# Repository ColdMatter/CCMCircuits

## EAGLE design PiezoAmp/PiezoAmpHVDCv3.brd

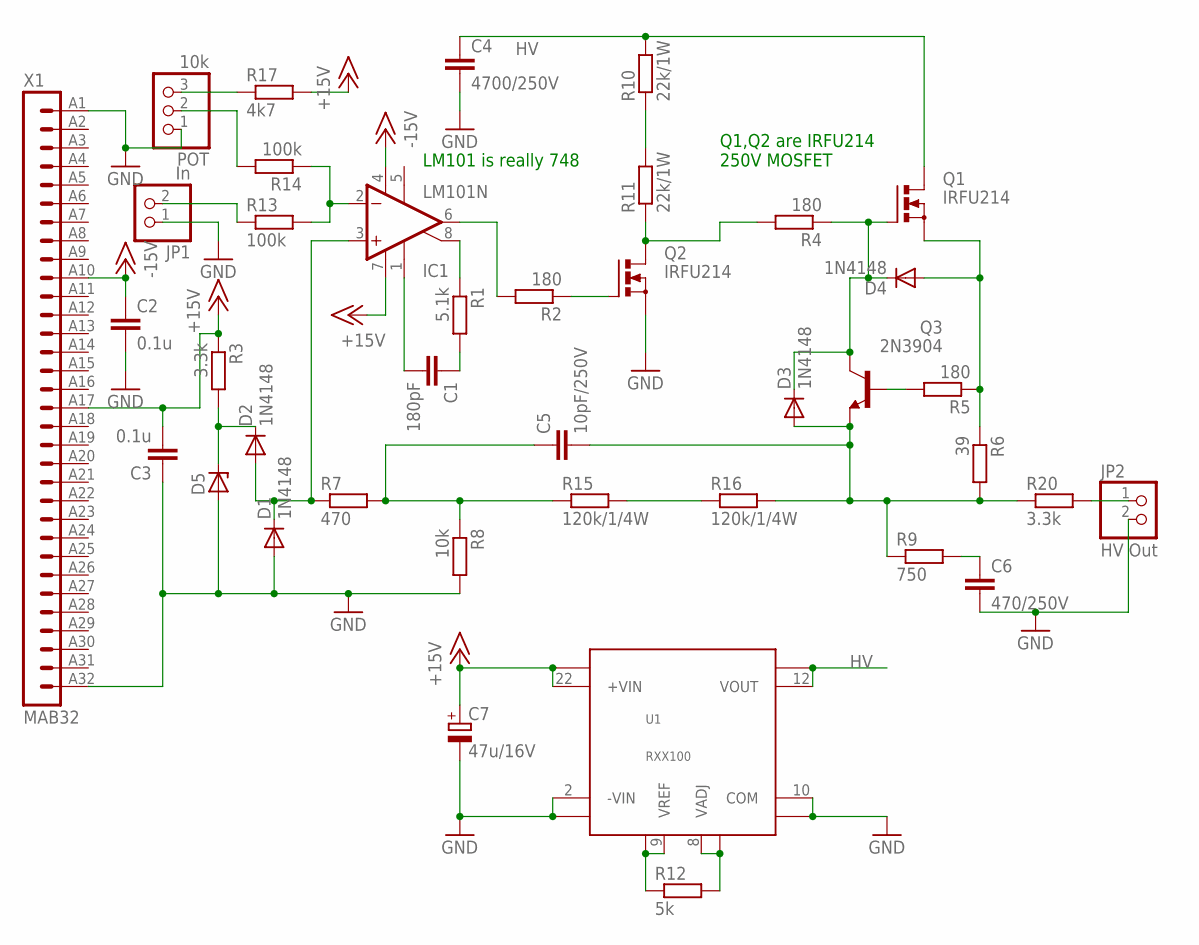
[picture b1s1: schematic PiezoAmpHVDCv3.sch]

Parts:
C1: 180pF; C050-030X075
C2, C3: 0.1u; C050-030X075
C4: 4700/250V; C075-032X103
C5: 10pF/250V; C075-032X103
C6: 470/250V; C075-032X103
C7: 47u/16V; SANYO-OSCON_F8
D1, D2, D3, D4: 1N4148; DO35-7
D5: ZENER-DIODEDO34-7; DO34Z7
IC1: LM101N; DIL08
JP1: In; 1X02
JP2: HV Out; 1X02
POT: 10k; 1X03
Q1, Q2: IRFU214; TO220BV
Q3: 2N3904; TO92
R1: 5.1k; 0204/7
R2, R4, R5: 180; 0204/7
R3, R20: 3.3k; 0204/7
R6: 39; 0204/7
R7: 470; 0204/7
R8: 10k; 0204/7
R9: 750; 0204/7
R10, R11: 22k/1W; 0411/15
R12: 5k; 0204/7
R13, R14: 100k; 0204/5
R15, R16: 120k/1/4W; 0411/15
R17: 4k7; 0204/5
U1: RXX100; RXXDIP
X1: MAB32

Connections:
+15V: C3.2, C7.+, IC1.7 (V+), R3.1, R17.2, U1.22 (+VIN), U1.23 (VIN2+), X1.A17 (17)
-15V: C2.1, IC1.4 (V-), X1.A10 (10)
GND: C2.2, C3.1, C4.2, C6.2, C7.-, D1.A, D5.A, JP1.1, JP2.2, POT.1, Q2.S, R8.2, U1.2 (-VIN), U1.3 (VIN2-), U1.10 (COM), U1.15 (COM2), X1.A1 (1), X1.A32 (32)
HV: C4.1, Q1.D, R10.2, U1.12 (VOUT), U1.13 (VOUT2)
unnamed: JP1.2, R13.1
unnamed: R10.1, R11.2
unnamed: Q2.G, R2.1
unnamed: Q2.D, R4.2, R11.1
unnamed: C6.1, R9.2
unnamed: R12.2, U1.8 (VADJ), U1.17 (VADJ2)
unnamed: IC1.8 (ON2), R1.1
unnamed: IC1.6 (OUT), R2.2
unnamed: R12.1, U1.9 (VREF), U1.16 (VREF2)
unnamed: IC1.2 (-IN), R13.2, R14.1
unnamed: D3.C, D4.C, Q1.G, Q3.1 (C), R4.1
unnamed: D4.A, Q1.S, R5.1, R6.1
unnamed: POT.2, R14.2
unnamed: Q3.2 (B), R5.2
unnamed: C5.2, D3.A, Q3.3 (E), R6.2, R9.1, R16.2, R20.1
unnamed: POT.3, R17.1
unnamed: R15.2, R16.1
unnamed: C5.1, R7.2, R8.1, R15.1
unnamed: D1.C, D2.A, IC1.3 (+IN), R7.1
unnamed: D2.C, D5.C, R3.2
unnamed: JP2.1, R20.2
unnamed: C1.1, R1.2
unnamed: C1.2, IC1.1 (ON1)

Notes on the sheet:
Q1,Q2 are IRFU214 250V MOSFET
LM101 is really 748

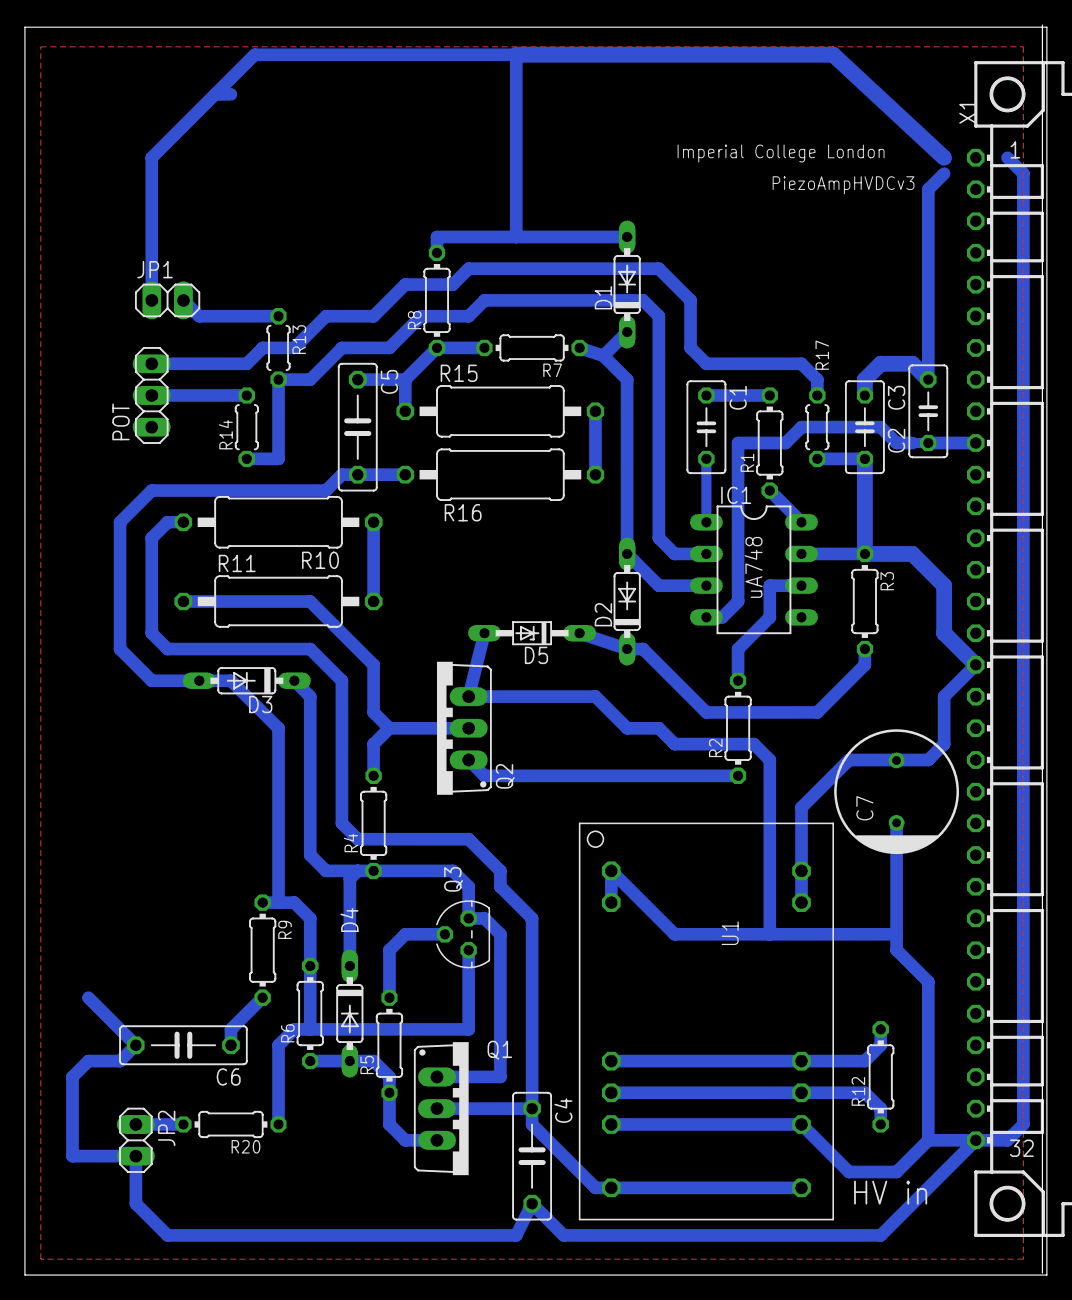
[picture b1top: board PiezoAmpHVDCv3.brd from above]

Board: 2 copper layers, 81.9 x 100.0 mm, 39 parts (0 on the bottom side), 27 nets.

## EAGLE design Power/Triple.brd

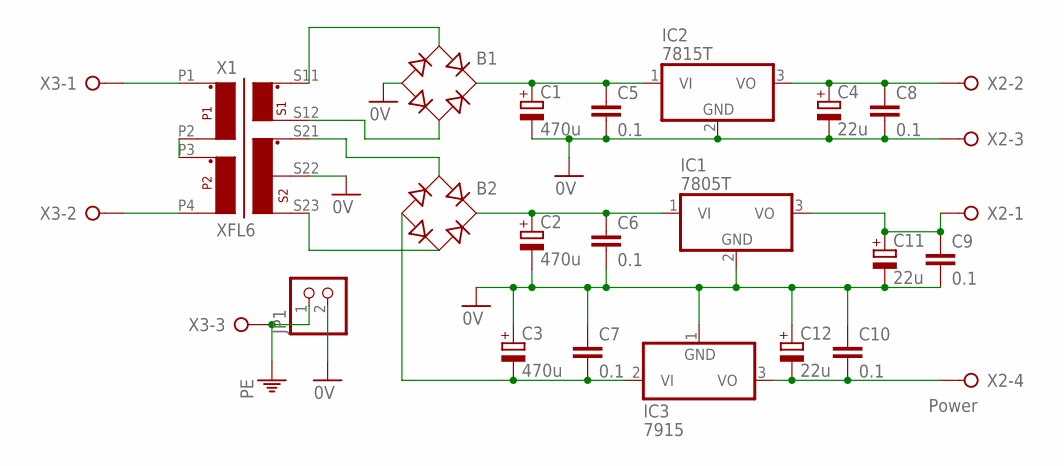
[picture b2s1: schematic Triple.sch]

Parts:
B1, B2: RB1A
C1, C2, C3: 470u; E5-10,5
C4, C11, C12: 22u; E5-10,5
C5, C6, C7, C8, C9, C10: 0.1; C050-025X075
IC1: 7805T; TO220H
IC2: 7815T; TO220H
IC3: 7915; TO220H
JP1: PINHD-1X2; 1X02
X1: XFL6; FL6
X2: Power; W237-4P
X3: W237-03P; W237-133

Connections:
0V: B1.-, C1.-, C2.-, C3.+, C4.-, C5.2, C6.2, C7.1, C8.2, C9.2, C10.1, C11.-, C12.+, IC1.2 (GND), IC2.2 (GND), IC3.1 (GND), JP1.2, X1.S22, X2.3
+5V: C4.+, C8.1, IC2.3 (VO), X2.2
+15V: C9.1, C11.+, IC1.3 (VO), X2.1
-15V: C10.2, C12.-, IC3.3 (VO), X2.4
unnamed: X1.P2, X1.P3
unnamed: X1.P1, X3.1
unnamed: X1.P4, X3.2
unnamed: B1.AC1, X1.S11
unnamed: B1.AC2, X1.S12
unnamed: B2.AC1, X1.S21
unnamed: B2.AC2, X1.S23
unnamed: B1.+, C1.+, C5.1, IC2.1 (VI)
PE: JP1.1, X3.3
VCC: B2.+, C2.+, C6.1, IC1.1 (VI)
VDD: B2.-, C3.-, C7.2, IC3.2 (VI)

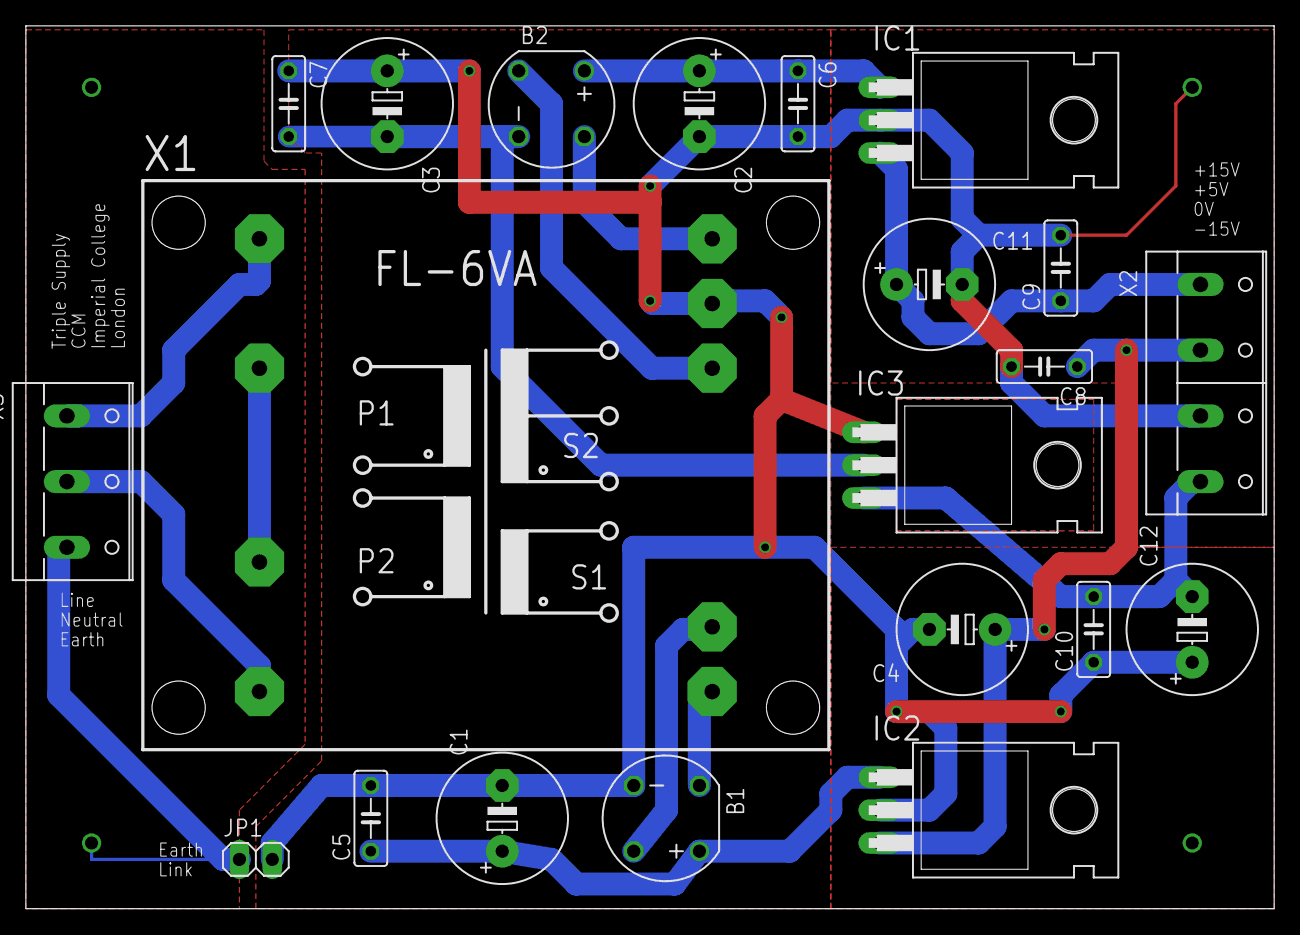
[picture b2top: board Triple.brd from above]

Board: 2 copper layers, 96.5 x 68.2 mm, 21 parts (0 on the bottom side), 15 nets.

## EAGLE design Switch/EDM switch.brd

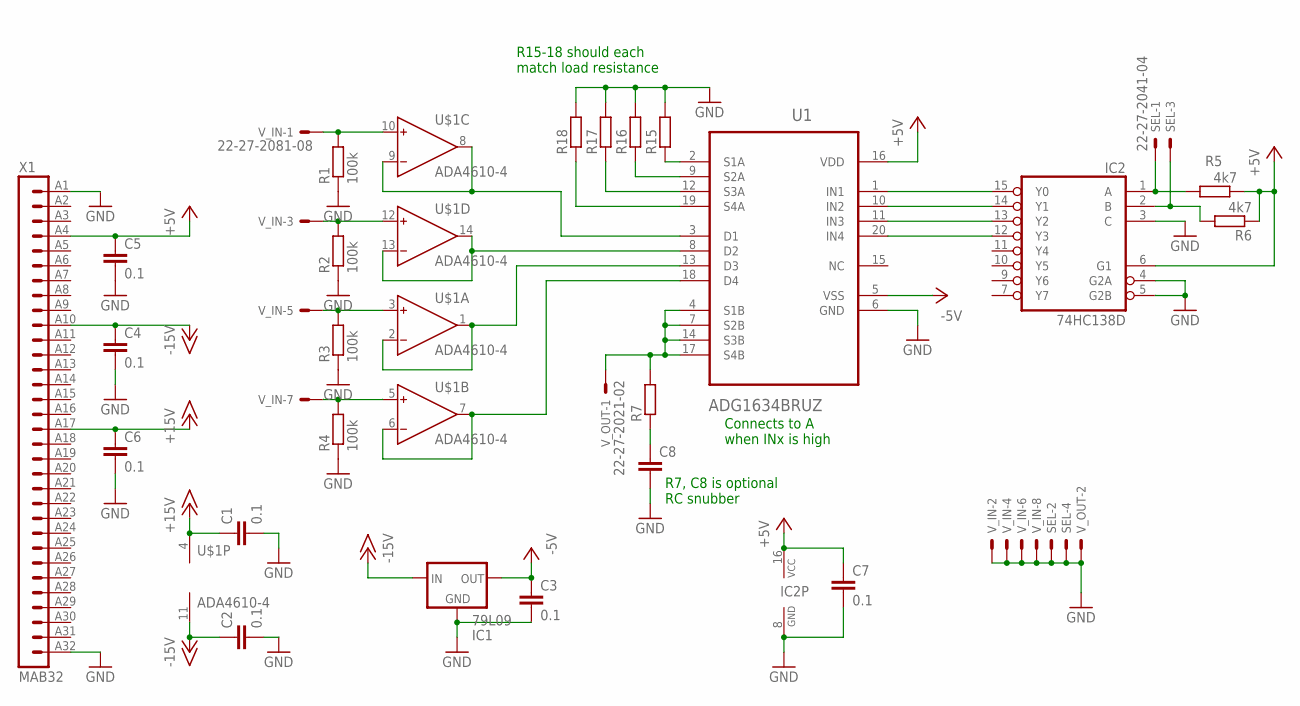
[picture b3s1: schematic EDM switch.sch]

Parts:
C1, C2, C3, C4, C5, C6, C7: 0.1; C0805
C8: C-EUC0805; C0805
IC1: 79L09; 79LXX
IC2: 74HC138D; SO16
R1, R2, R3, R4: 100k; R0805
R5, R6: 4k7; R0805
R7: R-EU_R0805; R0805
R15, R16, R17, R18: R-EU_0204/7; 0204/7
SEL: 22-27-2041-04; 6410-04
U1: ADG1634BRUZ; SOP65P640X120-20N
U$1: ADA4610-4; SO14
V_IN: 22-27-2081-08; 6410-08
V_OUT: 22-27-2021-02; 6410-02
X1: MAB32

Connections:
+5V: C5.1, C7.1, IC2.6 (G1), IC2.16 (VCC), R5.1, R6.1, U1.16 (VDD), X1.A4 (4)
+15V: C1.1, C6.1, U$1.4 (V+), X1.A17 (17)
-5V: C3.1, IC1.OUT, U1.5 (VSS)
-15V: C2.1, C4.1, IC1.IN, U$1.11 (V-), X1.A10 (10)
GND: C1.2, C2.2, C3.2, C4.2, C5.2, C6.2, C7.2, C8.2, IC1.GND, IC2.3 (C), IC2.4 (G2A), IC2.5 (G2B), IC2.8 (GND), R1.1, R2.1, R3.1, R4.1, R15.2, R16.2, R17.2, R18.2, SEL.2, SEL.4, U1.6 (GND), V_IN.2, V_IN.4, V_IN.6, V_IN.8, V_OUT.2, X1.A1 (1), X1.A32 (32)
unnamed: R1.2, U$1.10 (IN+), V_IN.1
unnamed: R2.2, U$1.12 (IN+), V_IN.3
unnamed: R3.2, U$1.3 (IN+), V_IN.5
unnamed: R4.2, U$1.5 (IN+), V_IN.7
unnamed: U1.3 (D1), U$1.8 (OUT), U$1.9 (IN-)
unnamed: U1.8 (D2), U$1.13 (IN-), U$1.14 (OUT)
unnamed: U1.13 (D3), U$1.1 (OUT), U$1.2 (IN-)
unnamed: U1.18 (D4), U$1.6 (IN-), U$1.7 (OUT)
unnamed: R15.1, U1.2 (S1A)
unnamed: R16.1, U1.9 (S2A)
unnamed: R17.1, U1.12 (S3A)
unnamed: R18.1, U1.19 (S4A)
unnamed: IC2.1 (A), R5.2, SEL.1
unnamed: R7.2, U1.4 (S1B), U1.7 (S2B), U1.14 (S3B), U1.17 (S4B), V_OUT.1
unnamed: IC2.2 (B), R6.2, SEL.3
unnamed: IC2.15 (Y0), U1.1 (IN1)
unnamed: IC2.14 (Y1), U1.10 (IN2)
unnamed: IC2.13 (Y2), U1.11 (IN3)
unnamed: IC2.12 (Y3), U1.20 (IN4)
unnamed: C8.1, R7.1

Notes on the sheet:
R15-18 should each match load resistance
Connects to A when INx is high
R7, C8 is optional RC snubber

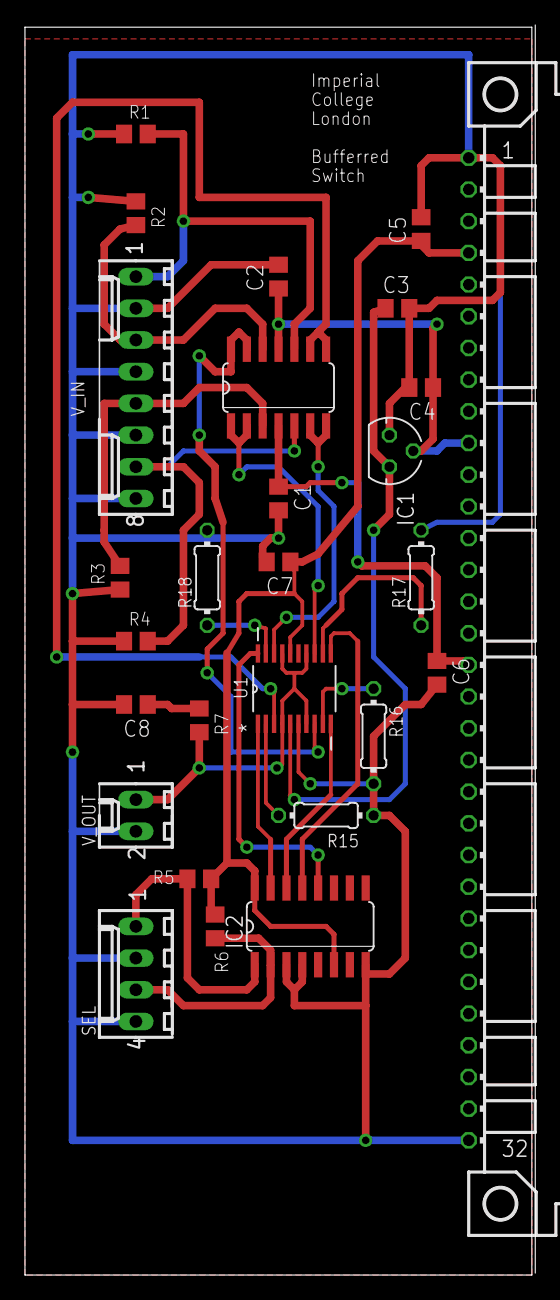
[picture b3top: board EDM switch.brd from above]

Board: 2 copper layers, 40.6 x 100.0 mm, 27 parts (0 on the bottom side), 25 nets.
